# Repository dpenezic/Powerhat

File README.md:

# Powerhat
An rpi hat to shut down the raspberry pi gracefully

This hat includes the eeprom and a real time clock. A normal 12v relay is "powered" by capacitors, and when the power is switched off, The rpi is told to shut down and the capacitors allow approx 45 seconds for it to shut down before the relay cuts the power

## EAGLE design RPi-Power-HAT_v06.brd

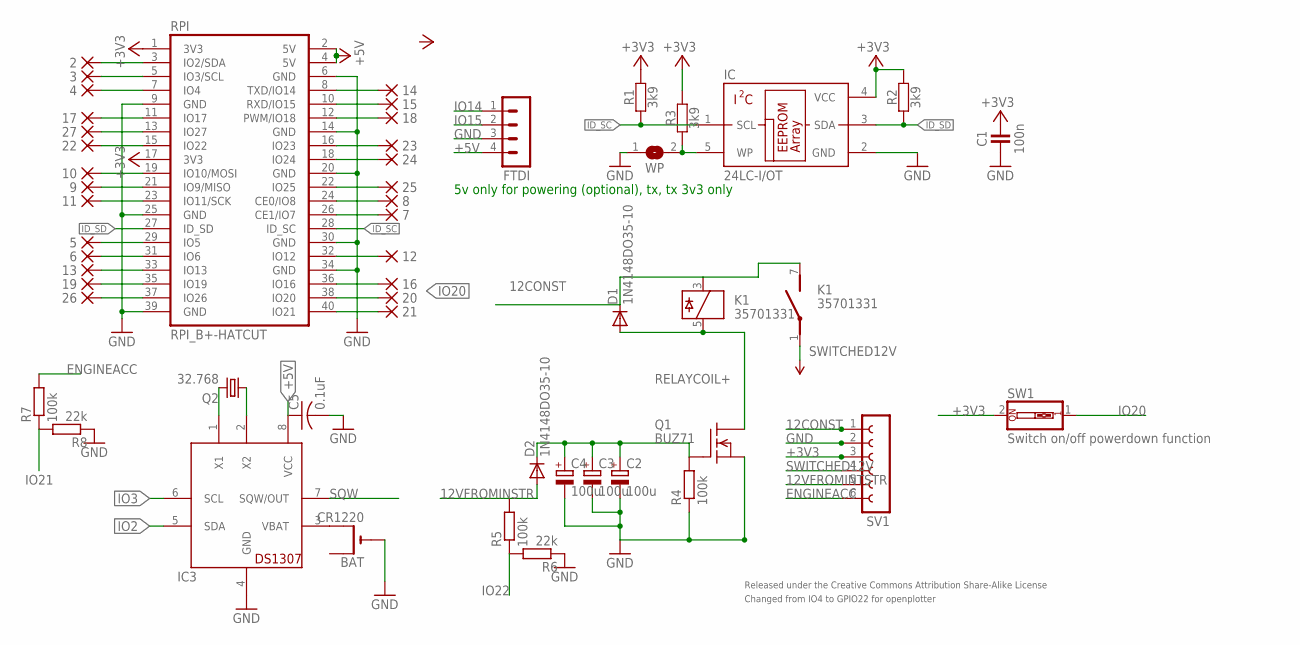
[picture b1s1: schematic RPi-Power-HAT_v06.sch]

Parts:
2, 3, 4, 5, 6, 7, 8, 9, 10, 11, 12, 13, 14, 15, 16, 17, 18, 19, 20, 21, 22, 23, 24, 25, 26, 27: PAD-1-1.6
BAT: CR1220; ADAFRUIT_CR1220-THM
C1: 100n; R0603
C2, C3, C4: 100u; E2-4
C5: 0.1uF; C025-025X050
D1, D2: 1N4148DO35-10; DO35-10
FTDI: MA04-1
IC: 24LC-I/OT; SOT23-5
IC3: DS1307; DIL08
K1: 35701331; REED
Q1: BUZ71; TO220
Q2: 32.768; TC38H
R1, R2, R3: 3k9; R0603
R4, R5, R7: 100k; 0207/2V
R6, R8: 22k; 0207/2V
RPI: RPI_B+-HATCUT; RPI-B+HAT_CUTOUT
SV1: FE06-1; FE06
SW1: Switch on/off powerdown function; EDG-01
WP: JUMPER2-NOCREAM; JUMPER2_NC

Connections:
12CONST: D1.C, K1.3, K1.7 (S), SV1.1
12VFROMINSTR: D2.A, R5.2
12VFROMINTSTR: SV1.5
+3V3: C1.2, IC.4 (VCC), R1.2, R2.2, R3.2, RPI.1 (3V3), RPI.17 (3V3), SV1.3, SW1.2
+5V: FTDI.4, IC3.8 (VCC), RPI.2 (5V), RPI.4 (5V)
ENGINEACC: R7.2, SV1.6
GND: BAT.-, C1.1, C2.-, C3.-, C4.-, C5.2, FTDI.3, IC.2 (GND), IC3.4 (GND), Q1.3 (S), R4.1, R6.1, R8.1, RPI.6 (GND), RPI.9 (GND), RPI.14 (GND), RPI.20 (GND), RPI.25 (GND), RPI.30 (GND), RPI.34 (GND), RPI.39 (GND), SV1.2, WP.1
ID_SC: IC.1 (SCL), R1.1, RPI.28 (ID_SC)
ID_SD: IC.3 (SDA), R2.1, RPI.27 (ID_SD)
IO2: 2.1, IC3.5 (SDA), RPI.3 (IO2/SDA)
IO3: 3.1, IC3.6 (SCL), RPI.5 (IO3/SCL)
IO4: 4.1, RPI.7 (IO4)
IO5: 5.1, RPI.29 (IO5)
IO6: 6.1, RPI.31 (IO6)
IO7: 7.1, RPI.26 (CE1/IO7)
IO8: 8.1, RPI.24 (CE0/IO8)
IO9: 9.1, RPI.21 (IO9/MISO)
IO10: 10.1, RPI.19 (IO10/MOSI)
IO11: 11.1, RPI.23 (IO11/SCK)
IO12: 12.1, RPI.32 (IO12)
IO13: 13.1, RPI.33 (IO13)
IO14: 14.1, FTDI.1, RPI.8 (TXD/IO14)
IO15: 15.1, FTDI.2, RPI.10 (RXD/IO15)
IO16: 16.1, RPI.36 (IO16)
IO17: 17.1, RPI.11 (IO17)
IO18: 18.1, RPI.12 (PWM/IO18)
IO19: 19.1, RPI.35 (IO19)
IO20: 20.1, RPI.38 (IO20), SW1.1
IO21: 21.1, R7.1, R8.2, RPI.40 (IO21)
IO22: 22.1, R5.1, R6.2, RPI.15 (IO22)
IO23: 23.1, RPI.16 (IO23)
IO24: 24.1, RPI.18 (IO24)
IO25: 25.1, RPI.22 (IO25)
IO26: 26.1, RPI.37 (IO26)
IO27: 27.1, RPI.13 (IO27)
unnamed: C2.+, C3.+, C4.+, D2.C, Q1.1 (G), R4.2
unnamed: IC3.1 (X1), Q2.2
unnamed: IC3.2 (X2), Q2.1
unnamed: BAT.+2 (+1), IC3.3 (VBAT)
RELAYCOIL+: D1.A, K1.5, Q1.2 (D)
SQW: IC3.7 (SQW/OUT)
SWITCHED12V: K1.1, SV1.4
WP: IC.5 (WP), R3.1, WP.2

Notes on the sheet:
Released under the Creative Commons Attribution Share-Alike License
5v only for powering (optional), tx, tx 3v3 only
Changed from IO4 to GPIO22 for openplotter

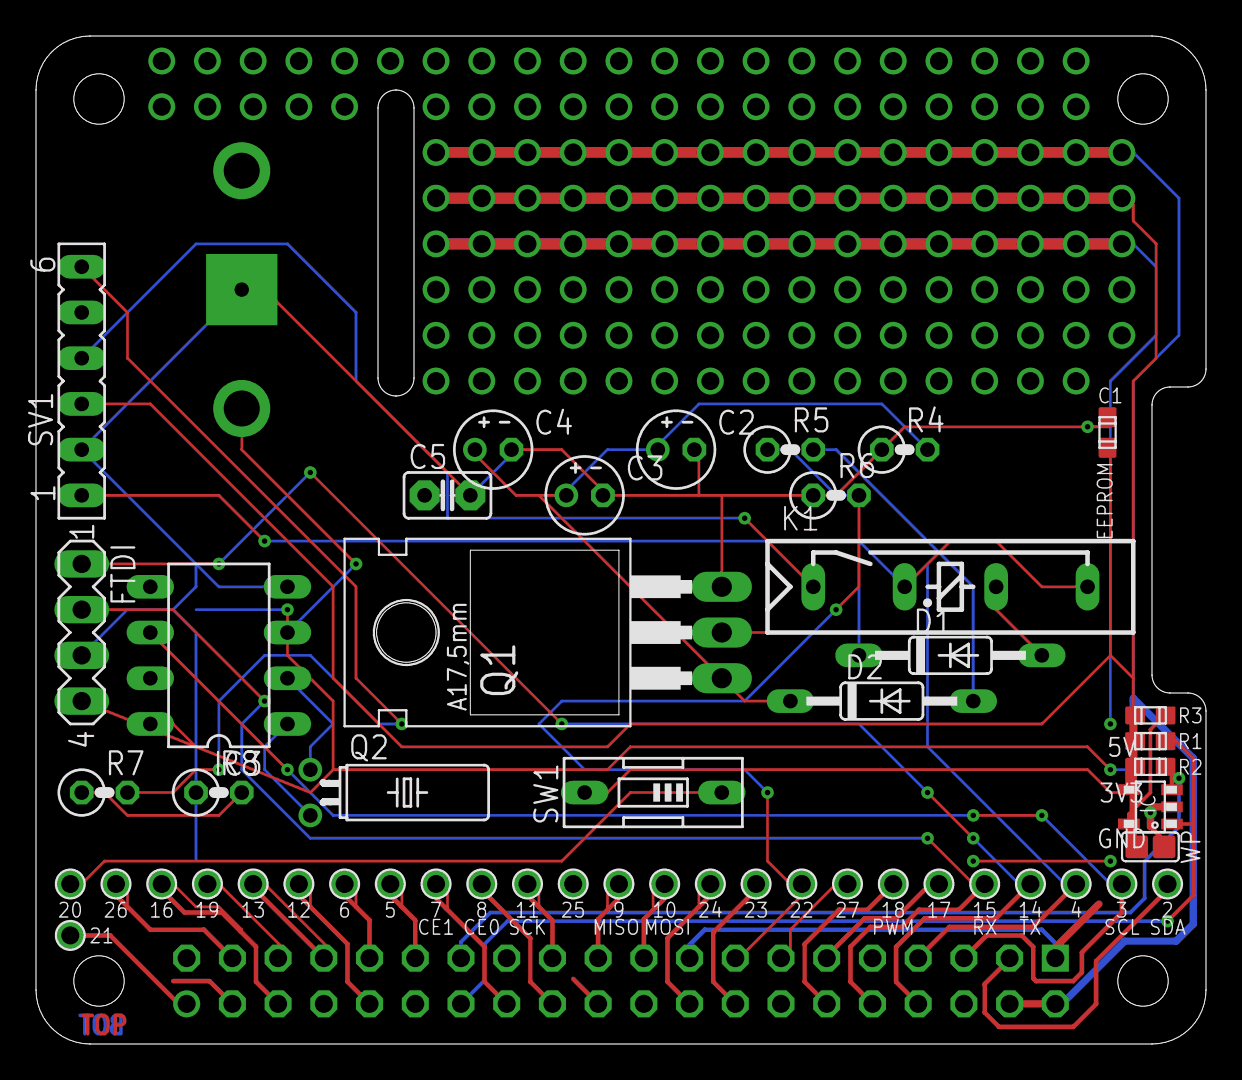
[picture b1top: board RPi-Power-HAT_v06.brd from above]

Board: 2 copper layers, 65.0 x 56.0 mm, 52 parts (1 on the bottom side), 41 nets.

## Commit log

2016-11-17 Readme
